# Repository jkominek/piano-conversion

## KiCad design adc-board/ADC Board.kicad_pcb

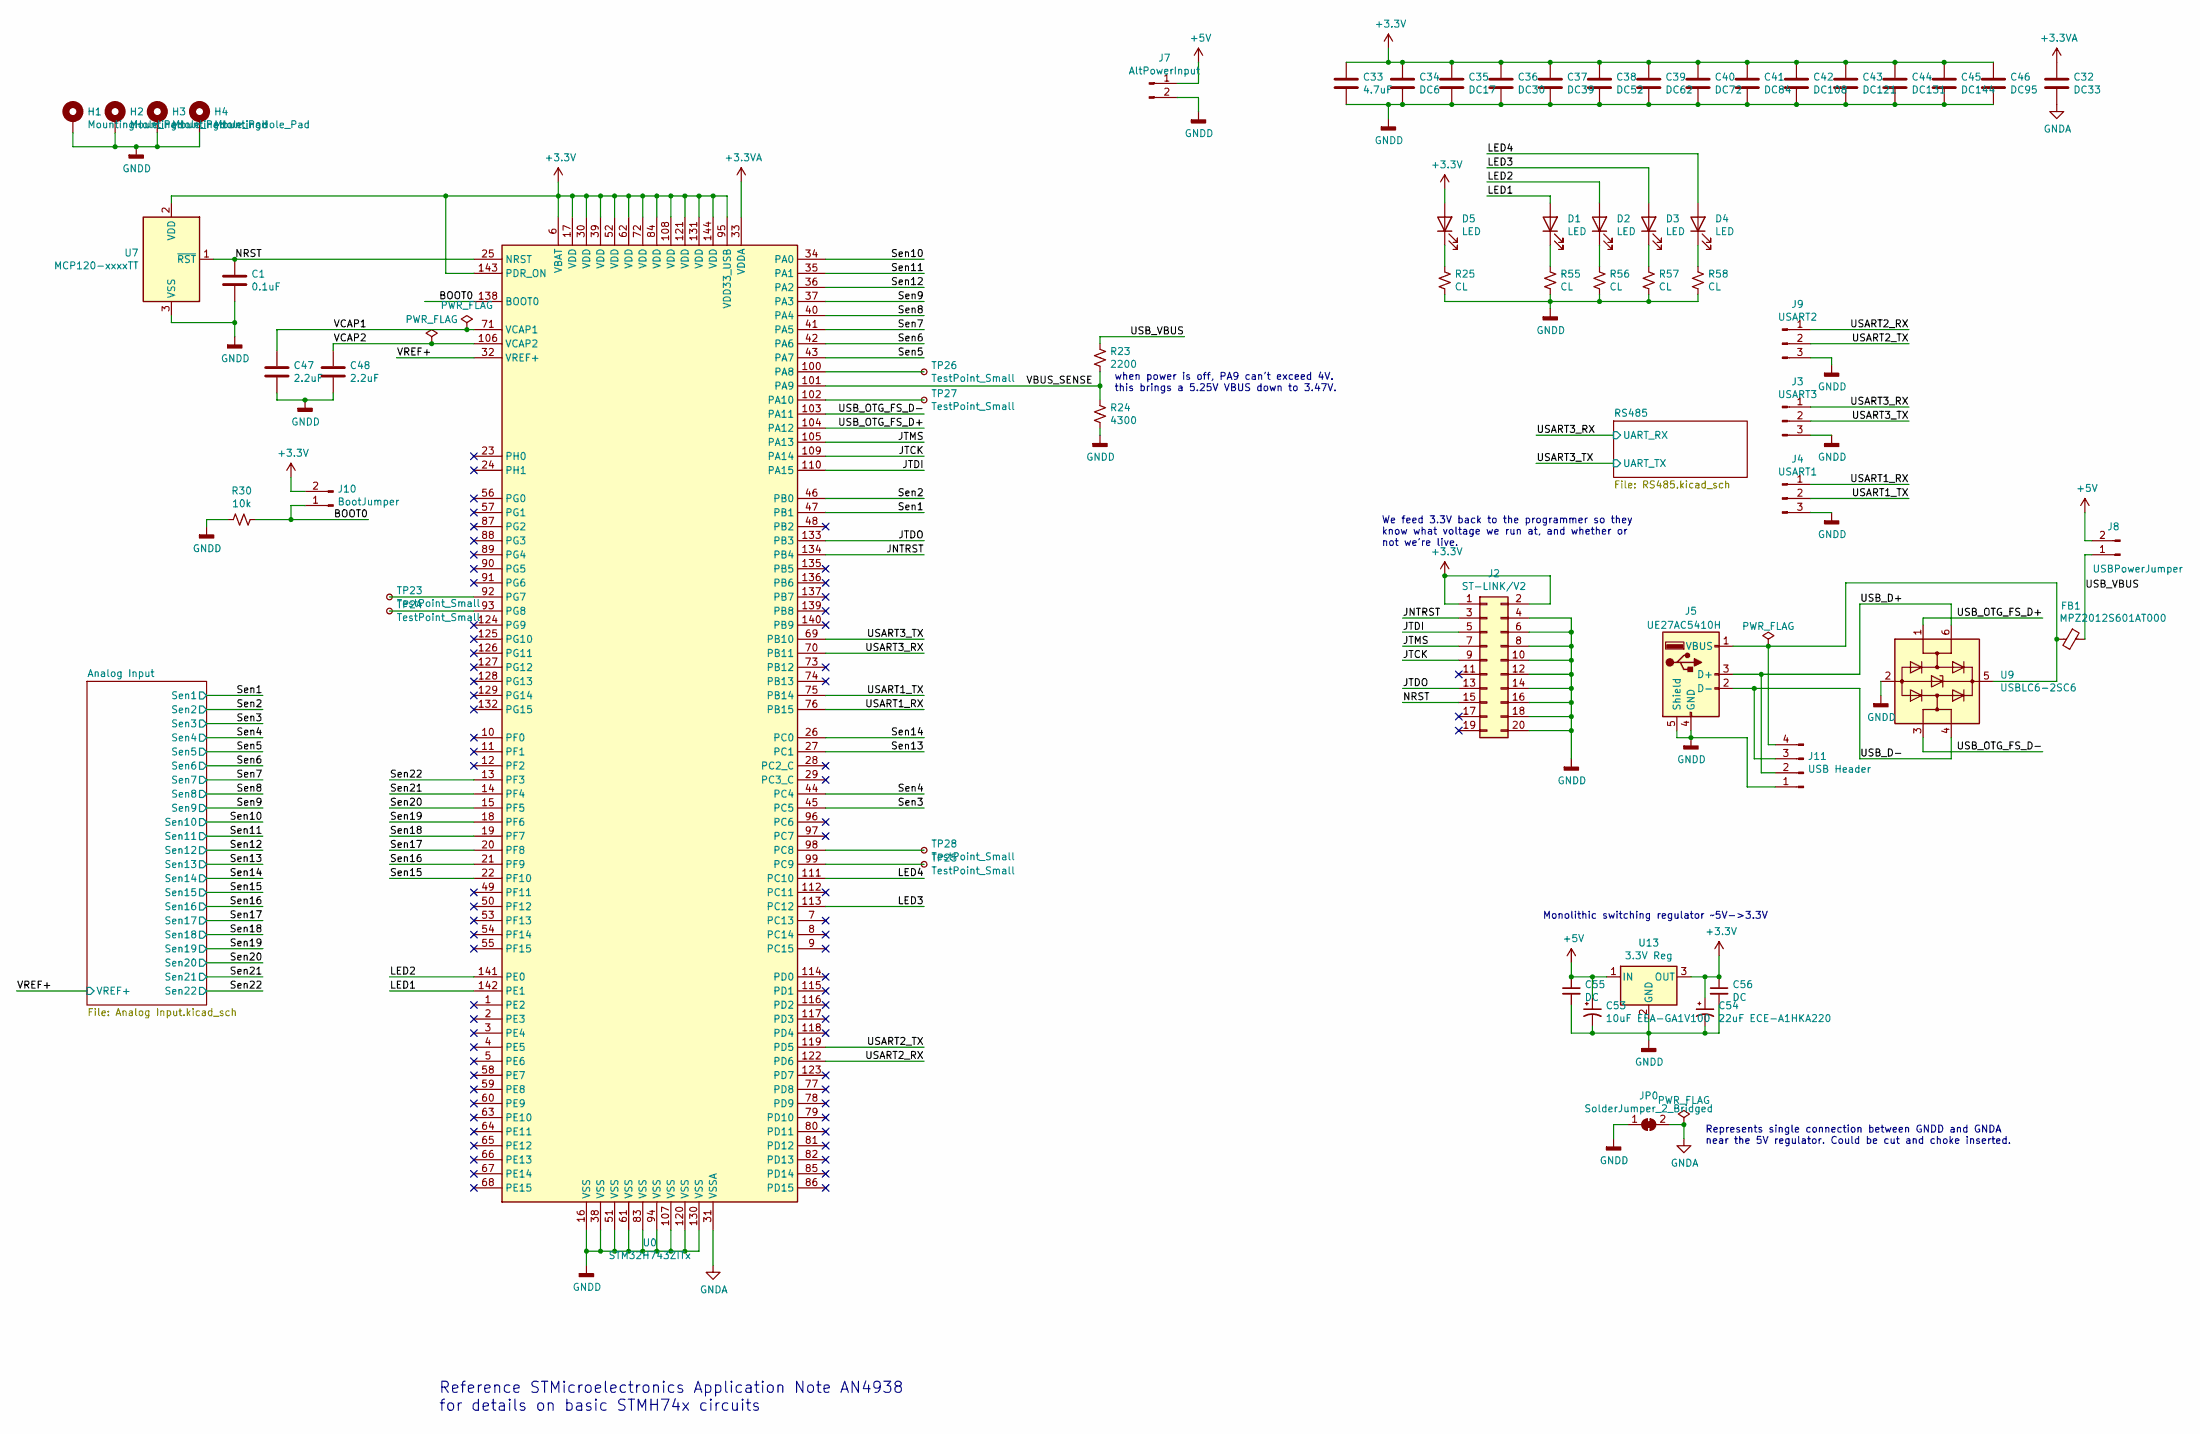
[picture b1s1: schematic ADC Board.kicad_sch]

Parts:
C1: 0.1uF; C_0805
C32: DC33; C_0805
C33: 4.7uF; C_0805
C34: DC6; C_0805
C35: DC17; C_0805
C36: DC30; C_0805
C37: DC39; C_0805
C38: DC52; C_0805
C39: DC62; C_0805
C40: DC72; C_0805
C41: DC84; C_0805
C42: DC108; C_0805
C43: DC121; C_0805
C44: DC131; C_0805
C45: DC144; C_0805
C46: DC95; C_0805
C47, C48: 2.2uF; C_0805
C53: 10uF EEA-GA1V100; CP_Elec_5x5.3
C54: 22uF ECE-A1HKA220; CP_Elec_6.3x5.3
C55, C56: DC; C_0805
D1, D2, D3, D4, D5: LED; LED_0805_HandSoldering
FB1: MPZ2012S601AT000; L_0805
H1, H2, H3, H4: MountingHole_Pad; MountingHole_3.2mm_M3_Pad_Via
J2: ST-LINK/V2; Pin_Header_Straight_2x10_Pitch2.54mm
J3: USART3; Pin_Header_Straight_1x03_Pitch2.54mm
J4: USART1; Pin_Header_Straight_1x03_Pitch2.54mm
J5: UE27AC5410H; USB_A_Molex_67643_Horizontal
J7: AltPowerInput; Pin_Header_Straight_1x02_Pitch2.54mm
J8: USBPowerJumper; Pin_Header_Straight_1x02_Pitch2.54mm
J9: USART2; Pin_Header_Straight_1x03_Pitch2.54mm
J10: BootJumper; Pin_Header_Straight_1x02_Pitch2.54mm
J11: USB Header; Pin_Header_Straight_1x04_Pitch2.54mm
JP0: SolderJumper_2_Bridged; SolderJumper-2_P1.3mm_Bridged_RoundedPad1.0x1.5mm
R23: 2200; R_0805
R24: 4300; R_0805
R25, R55, R56, R57, R58: CL; R_0805
R30: 10k; R_0805
TP23, TP24, TP25, TP26, TP27, TP28: TestPoint_Small; TestPoint_Pad_D1.5mm
U0: STM32H743ZITx; LQFP-144_20x20mm_Pitch0.5mm
U7: MCP120-xxxxTT; SOT-23
U9: USBLC6-2SC6; SOT-23-6_Handsoldering
U13: 3.3V Reg; TO-220-3_Vertical

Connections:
+3.3VA: C32.1, U0.33 (VDDA); also elsewhere on the board
+3V3: C33.1, C34.1, C35.1, C36.1, C37.1, C38.1, C39.1, C40.1, C41.1, C42.1, C43.1, C44.1, C45.1, C46.1, C54.1, C56.1, D5.2 (A), J2.1, J2.2, J10.2, U0.6 (VBAT), U0.17 (VDD), U0.30 (VDD), U0.39 (VDD), U0.52 (VDD), U0.62 (VDD), U0.72 (VDD), U0.84 (VDD), U0.95 (VDD33_USB), U0.108 (VDD), U0.121 (VDD), U0.131 (VDD), U0.143 (PDR_ON), U0.144 (VDD), U7.2 (VDD), U13.3 (OUT); also elsewhere on the board
+5V: C53.1, C55.1, J7.1, J8.2, U13.1 (IN); also elsewhere on the board
/BOOT0: J10.1, R30.1, U0.138 (BOOT0)
/JNTRST: J2.3, U0.134 (PB4)
/JTCK: J2.9, U0.109 (PA14)
/JTDI: J2.5, U0.110 (PA15)
/JTDO: J2.13, U0.133 (PB3)
/JTMS: J2.7, U0.105 (PA13)
/LED1: D1.2 (A), U0.142 (PE1)
/LED2: D2.2 (A), U0.141 (PE0)
/LED3: D3.2 (A), U0.113 (PC12)
/LED4: D4.2 (A), U0.111 (PC10)
/NRST: C1.1, J2.15, U0.25 (NRST), U7.1 (~RST)
/Sen1: U0.47 (PB1); also elsewhere on the board
/Sen2: U0.46 (PB0); also elsewhere on the board
/Sen3: U0.45 (PC5); also elsewhere on the board
/Sen4: U0.44 (PC4); also elsewhere on the board
/Sen5: U0.43 (PA7); also elsewhere on the board
/Sen6: U0.42 (PA6); also elsewhere on the board
/Sen7: U0.41 (PA5); also elsewhere on the board
/Sen8: U0.40 (PA4); also elsewhere on the board
/Sen9: U0.37 (PA3); also elsewhere on the board
/Sen10: U0.34 (PA0); also elsewhere on the board
/Sen11: U0.35 (PA1); also elsewhere on the board
/Sen12: U0.36 (PA2); also elsewhere on the board
/Sen13: U0.27 (PC1); also elsewhere on the board
/Sen14: U0.26 (PC0); also elsewhere on the board
/Sen15: U0.22 (PF10); also elsewhere on the board
/Sen16: U0.21 (PF9); also elsewhere on the board
/Sen17: U0.20 (PF8); also elsewhere on the board
/Sen18: U0.19 (PF7); also elsewhere on the board
/Sen19: U0.18 (PF6); also elsewhere on the board
/Sen20: U0.15 (PF5); also elsewhere on the board
/Sen21: U0.14 (PF4); also elsewhere on the board
/Sen22: U0.13 (PF3); also elsewhere on the board
/USART1_RX: J4.1, U0.76 (PB15)
/USART1_TX: J4.2, U0.75 (PB14)
/USART2_RX: J9.1, U0.122 (PD6)
/USART2_TX: J9.2, U0.119 (PD5)
/USART3_RX: J3.1, U0.70 (PB11); also elsewhere on the board
/USART3_TX: J3.2, U0.69 (PB10); also elsewhere on the board
/USB_D+: J5.3 (D+), J11.2, U9.6 (I/O1)
/USB_D-: J5.2 (D-), J11.3, U9.4 (I/O2)
/USB_OTG_FS_D+: U0.104 (PA12), U9.1 (I/O1)
/USB_OTG_FS_D-: U0.103 (PA11), U9.3 (I/O2)
/USB_VBUS: FB1.1, J8.1, R23.1
/VBUS_SENSE: R23.2, R24.1, U0.101 (PA9)
/VCAP1: C47.1, U0.71 (VCAP1)
/VCAP2: C48.1, U0.106 (VCAP2)
/VREF+: U0.32 (VREF+); also elsewhere on the board
GNDA: C32.2, JP0.2 (B), U0.31 (VSSA); also elsewhere on the board
GNDD: C1.2, C33.2, C34.2, C35.2, C36.2, C37.2, C38.2, C39.2, C40.2, C41.2, C42.2, C43.2, C44.2, C45.2, C46.2, C47.2, C48.2, C53.2, C54.2, C55.2, C56.2, H1.1, H2.1, H3.1, H4.1, J2.4, J2.6, J2.8, J2.10, J2.12, J2.14, J2.16, J2.18, J2.20, J3.3, J4.3, J5.4 (GND), J5.5 (Shield), J7.2, J9.3, J11.1, JP0.1 (A), R24.2, R25.2, R30.2, R55.2, R56.2, R57.2, R58.2, U0.16 (VSS), U0.38 (VSS), U0.51 (VSS), U0.61 (VSS), U0.83 (VSS), U0.94 (VSS), U0.107 (VSS), U0.120 (VSS), U0.130 (VSS), U7.3 (VSS), U9.2 (GND), U13.2 (GND); also elsewhere on the board
unnamed: D1.1 (K), R55.1
unnamed: D2.1 (K), R56.1
unnamed: D3.1 (K), R57.1
unnamed: D4.1 (K), R58.1
unnamed: D5.1 (K), R25.1
unnamed: FB1.2, J5.1 (VBUS), J11.4, U9.5 (VBUS)
unnamed: TP23.1, U0.92 (PG7)
unnamed: TP24.1, U0.93 (PG8)
unnamed: TP25.1, U0.99 (PC9)
unnamed: TP26.1, U0.100 (PA8)
unnamed: TP27.1, U0.102 (PA10)
unnamed: TP28.1, U0.98 (PC8)

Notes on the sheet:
Monolithic switching regulator ~5V->3.3V
We feed 3.3V back to the programmer so they know what voltage we run at, and whether or not we're live.
Reference STMicroelectronics Application Note AN4938 for details on basic STMH74x circuits
when power is off, PA9 can't exceed 4V. this brings a 5.25V VBUS down to 3.47V.
Represents single connection between GNDD and GNDA near the 5V regulator. Could be cut and choke inserted.

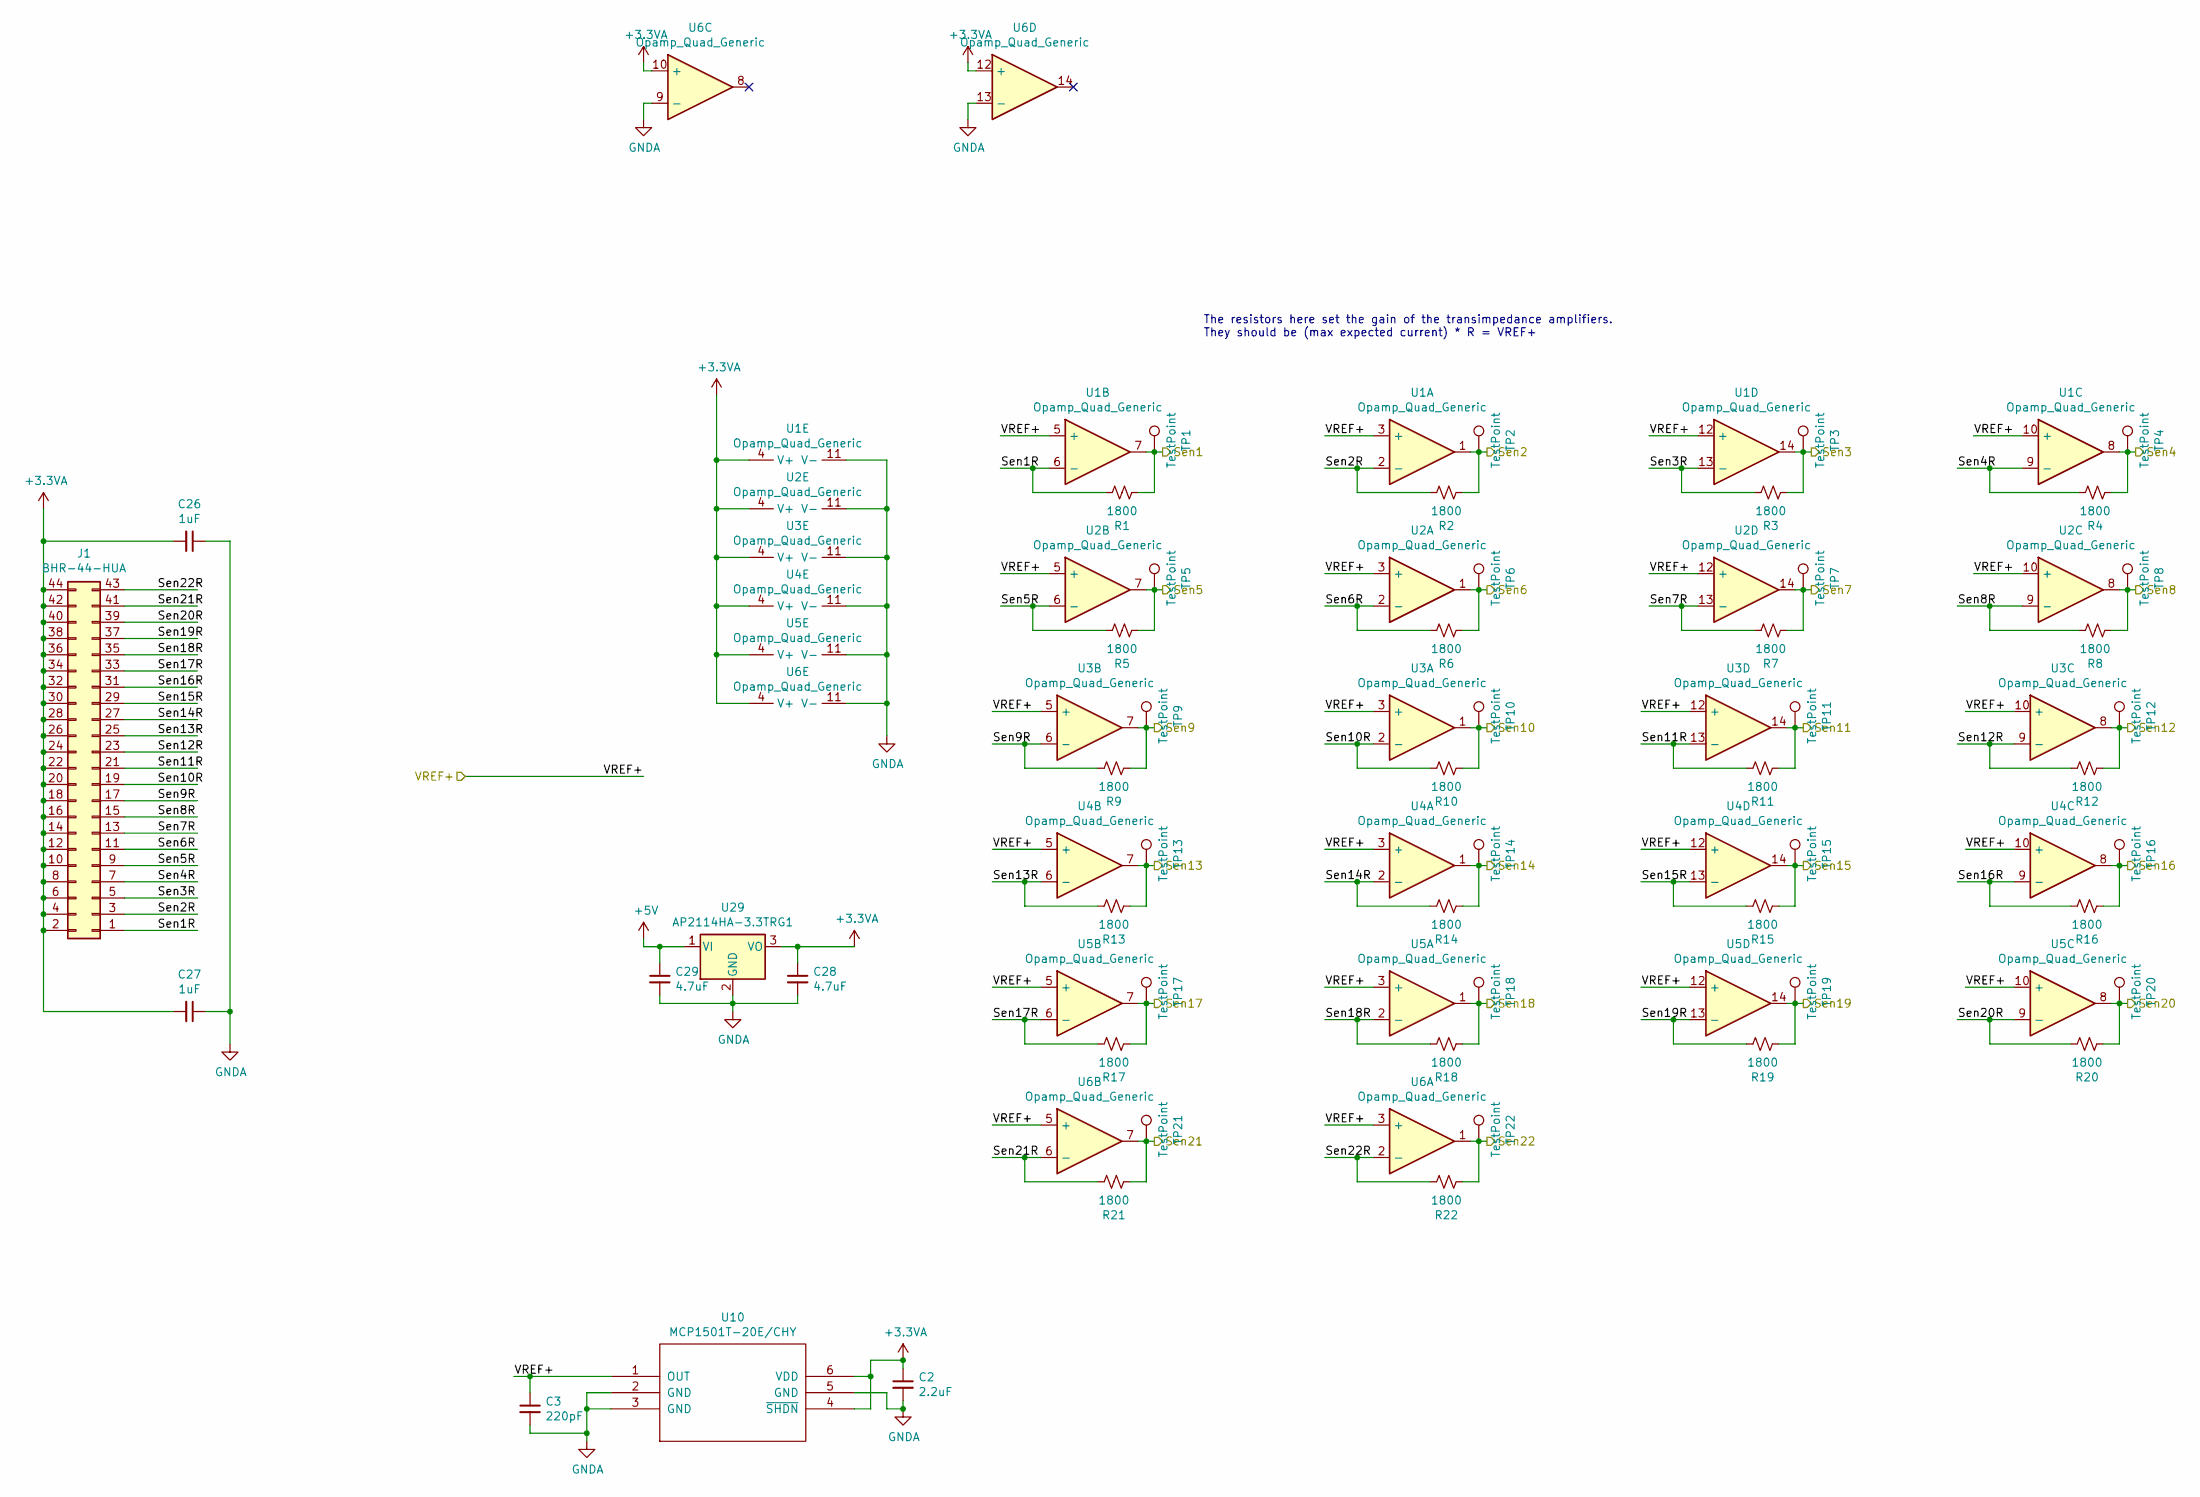
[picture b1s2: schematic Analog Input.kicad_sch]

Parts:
C2: 2.2uF; C_0805
C3: 220pF; C_0805
C26, C27: 1uF; C_0805
C28, C29: 4.7uF; C_0805
J1: BHR-44-HUA; Pin_Header_Angled_2x22_Pitch2.54mm
R1, R2, R3, R4, R5, R6, R7, R8, R9, R10, R11, R12, R13, R14, R15, R16, R17, R18, R19, R20, R21, R22: 1800; R_0805
TP1, TP2, TP3, TP4, TP5, TP6, TP7, TP8, TP9, TP10, TP11, TP12, TP13, TP14, TP15, TP16, TP17, TP18, TP19, TP20, TP21, TP22: TestPoint; TestPoint_Pad_D1.0mm
U1, U2, U3, U4, U5, U6: Opamp_Quad_Generic; TSSOP-14_4.4x5mm_Pitch0.65mm
U10: MCP1501T-20E/CHY; SOT-23-6_Handsoldering
U29: AP2114HA-3.3TRG1; SOT-223-3_TabPin2

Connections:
+3.3VA: C2.1, C26.2, C27.2, C28.1, J1.2, J1.4, J1.6, J1.8, J1.10, J1.12, J1.14, J1.16, J1.18, J1.20, J1.22, J1.24, J1.26, J1.28, J1.30, J1.32, J1.34, J1.36, J1.38, J1.40, J1.42, J1.44, U1.4 (V+), U2.4 (V+), U3.4 (V+), U4.4 (V+), U5.4 (V+), U6.4 (V+), U6.10 (+), U6.12 (+), U10.4 (~SHDN), U10.6 (VDD), U29.3 (VO); also elsewhere on the board
+5V: C29.1, U29.1 (VI); also elsewhere on the board
/Analog Input/Sen1R: J1.1, R1.1, U1.6 (-)
/Analog Input/Sen2R: J1.3, R2.1, U1.2 (-)
/Analog Input/Sen3R: J1.5, R3.1, U1.13 (-)
/Analog Input/Sen4R: J1.7, R4.1, U1.9 (-)
/Analog Input/Sen5R: J1.9, R5.1, U2.6 (-)
/Analog Input/Sen6R: J1.11, R6.1, U2.2 (-)
/Analog Input/Sen7R: J1.13, R7.1, U2.13 (-)
/Analog Input/Sen8R: J1.15, R8.1, U2.9 (-)
/Analog Input/Sen9R: J1.17, R9.1, U3.6 (-)
/Analog Input/Sen10R: J1.19, R10.1, U3.2 (-)
/Analog Input/Sen11R: J1.21, R11.1, U3.13 (-)
/Analog Input/Sen12R: J1.23, R12.1, U3.9 (-)
/Analog Input/Sen13R: J1.25, R13.1, U4.6 (-)
/Analog Input/Sen14R: J1.27, R14.1, U4.2 (-)
/Analog Input/Sen15R: J1.29, R15.1, U4.13 (-)
/Analog Input/Sen16R: J1.31, R16.1, U4.9 (-)
/Analog Input/Sen17R: J1.33, R17.1, U5.6 (-)
/Analog Input/Sen18R: J1.35, R18.1, U5.2 (-)
/Analog Input/Sen19R: J1.37, R19.1, U5.13 (-)
/Analog Input/Sen20R: J1.39, R20.1, U5.9 (-)
/Analog Input/Sen21R: J1.41, R21.1, U6.6 (-)
/Analog Input/Sen22R: J1.43, R22.1, U6.2 (-)
/Sen1: R1.2, TP1.1, U1.7; also elsewhere on the board
/Sen2: R2.2, TP2.1, U1.1; also elsewhere on the board
/Sen3: R3.2, TP3.1, U1.14; also elsewhere on the board
/Sen4: R4.2, TP4.1, U1.8; also elsewhere on the board
/Sen5: R5.2, TP5.1, U2.7; also elsewhere on the board
/Sen6: R6.2, TP6.1, U2.1; also elsewhere on the board
/Sen7: R7.2, TP7.1, U2.14; also elsewhere on the board
/Sen8: R8.2, TP8.1, U2.8; also elsewhere on the board
/Sen9: R9.2, TP9.1, U3.7; also elsewhere on the board
/Sen10: R10.2, TP10.1, U3.1; also elsewhere on the board
/Sen11: R11.2, TP11.1, U3.14; also elsewhere on the board
/Sen12: R12.2, TP12.1, U3.8; also elsewhere on the board
/Sen13: R13.2, TP13.1, U4.7; also elsewhere on the board
/Sen14: R14.2, TP14.1, U4.1; also elsewhere on the board
/Sen15: R15.2, TP15.1, U4.14; also elsewhere on the board
/Sen16: R16.2, TP16.1, U4.8; also elsewhere on the board
/Sen17: R17.2, TP17.1, U5.7; also elsewhere on the board
/Sen18: R18.2, TP18.1, U5.1; also elsewhere on the board
/Sen19: R19.2, TP19.1, U5.14; also elsewhere on the board
/Sen20: R20.2, TP20.1, U5.8; also elsewhere on the board
/Sen21: R21.2, TP21.1, U6.7; also elsewhere on the board
/Sen22: R22.2, TP22.1, U6.1; also elsewhere on the board
/VREF+: C3.1, U1.3 (+), U1.5 (+), U1.10 (+), U1.12 (+), U2.3 (+), U2.5 (+), U2.10 (+), U2.12 (+), U3.3 (+), U3.5 (+), U3.10 (+), U3.12 (+), U4.3 (+), U4.5 (+), U4.10 (+), U4.12 (+), U5.3 (+), U5.5 (+), U5.10 (+), U5.12 (+), U6.3 (+), U6.5 (+), U10.1 (OUT); also elsewhere on the board
GNDA: C2.2, C3.2, C26.1, C27.1, C28.2, C29.2, U1.11 (V-), U2.11 (V-), U3.11 (V-), U4.11 (V-), U5.11 (V-), U6.9 (-), U6.11 (V-), U6.13 (-), U10.2 (GND), U10.3 (GND), U10.5 (GND), U29.2 (GND); also elsewhere on the board

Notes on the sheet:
The resistors here set the gain of the transimpedance amplifiers. They should be (max expected current) * R =~{} VREF+

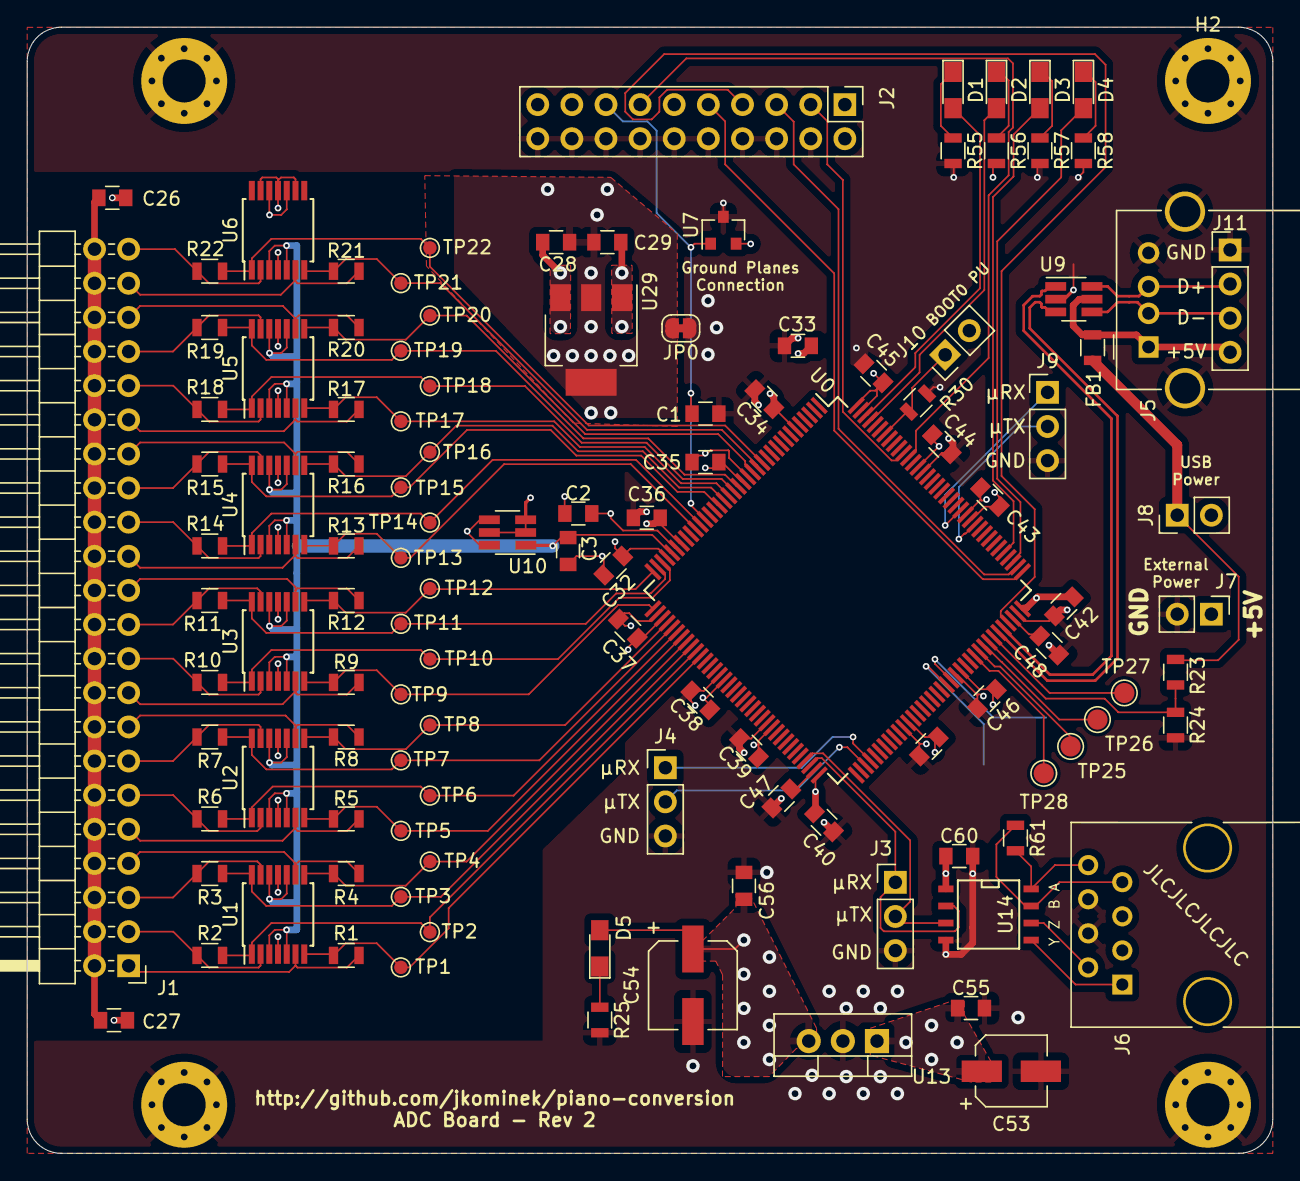
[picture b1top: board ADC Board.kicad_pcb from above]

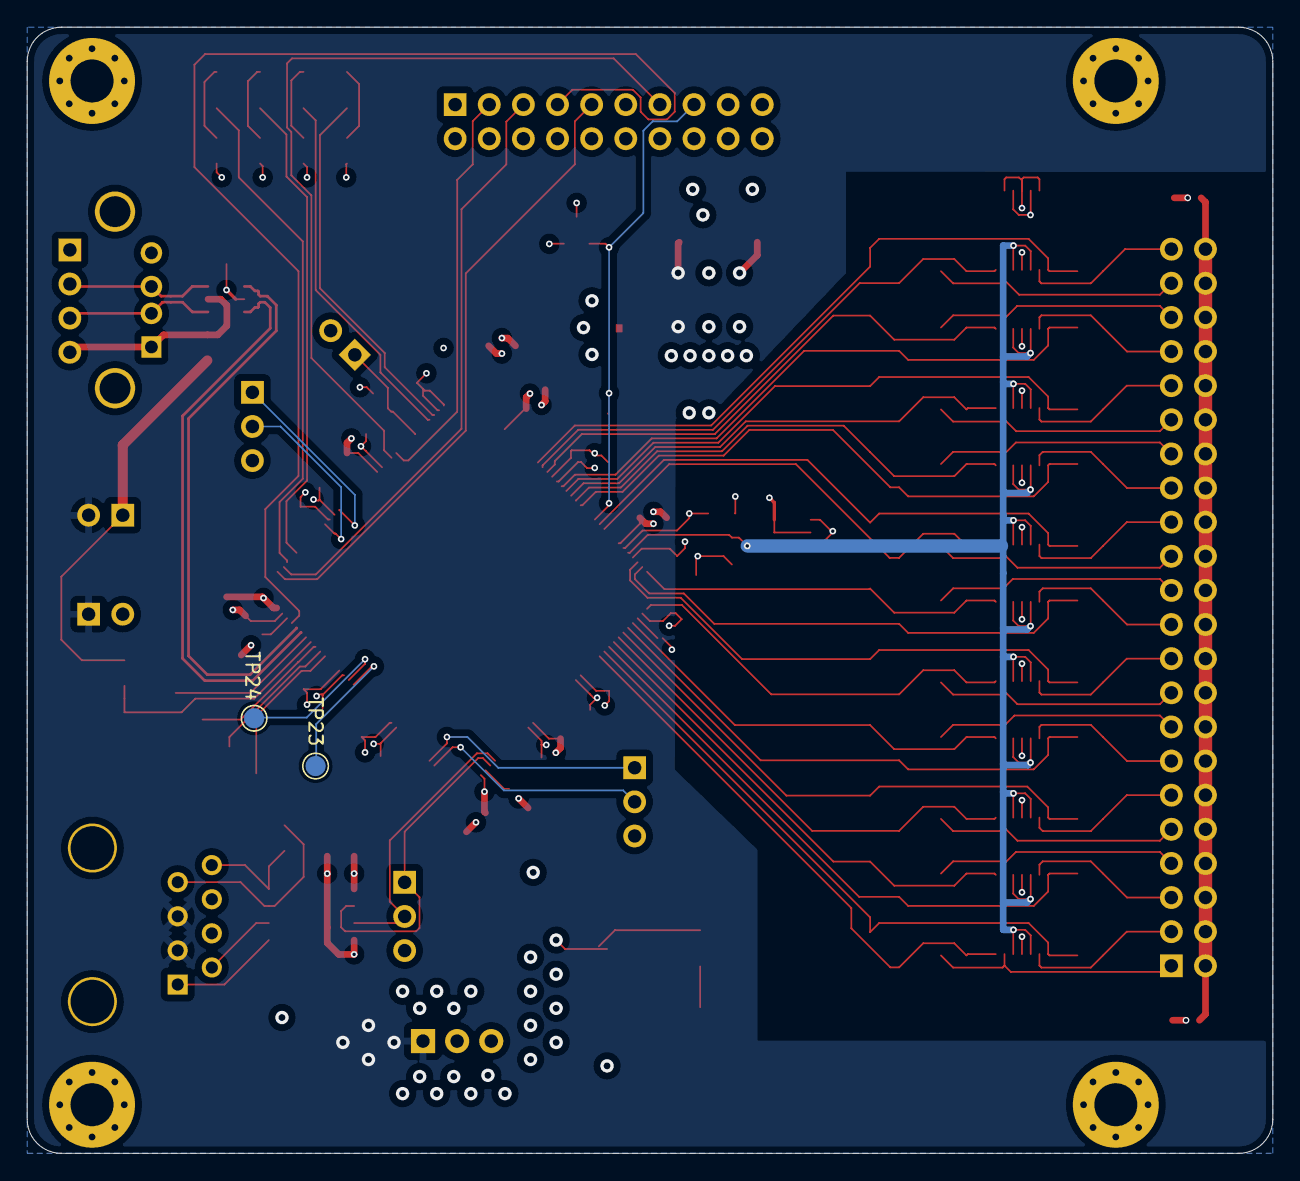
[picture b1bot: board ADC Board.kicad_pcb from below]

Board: 4 copper layers, 92.7 x 83.8 mm, 123 parts (2 on the bottom side), 91 nets.

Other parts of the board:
C60: DC; C_0805
J6: 54601-908WPLF; RJ45_8
R61: 120; R_0805
U14: ISL83490; SOIC-8-N

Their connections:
+3V3: C60.1, U14.1 (VCC); also elsewhere on the board
+5V: J6.3, J6.5; also elsewhere on the board
/RS485/A: J6.8, R61.2, U14.8 (A)
/RS485/B: J6.7, R61.1, U14.7 (B)
/RS485/Y: J6.1, U14.5 (Y)
/RS485/Z: J6.2, U14.6 (Z)
/USART3_RX: U14.2 (RO); also elsewhere on the board
/USART3_TX: U14.3 (DI); also elsewhere on the board
GNDD: C60.2, J6.4, J6.6, U14.4 (GND); also elsewhere on the board

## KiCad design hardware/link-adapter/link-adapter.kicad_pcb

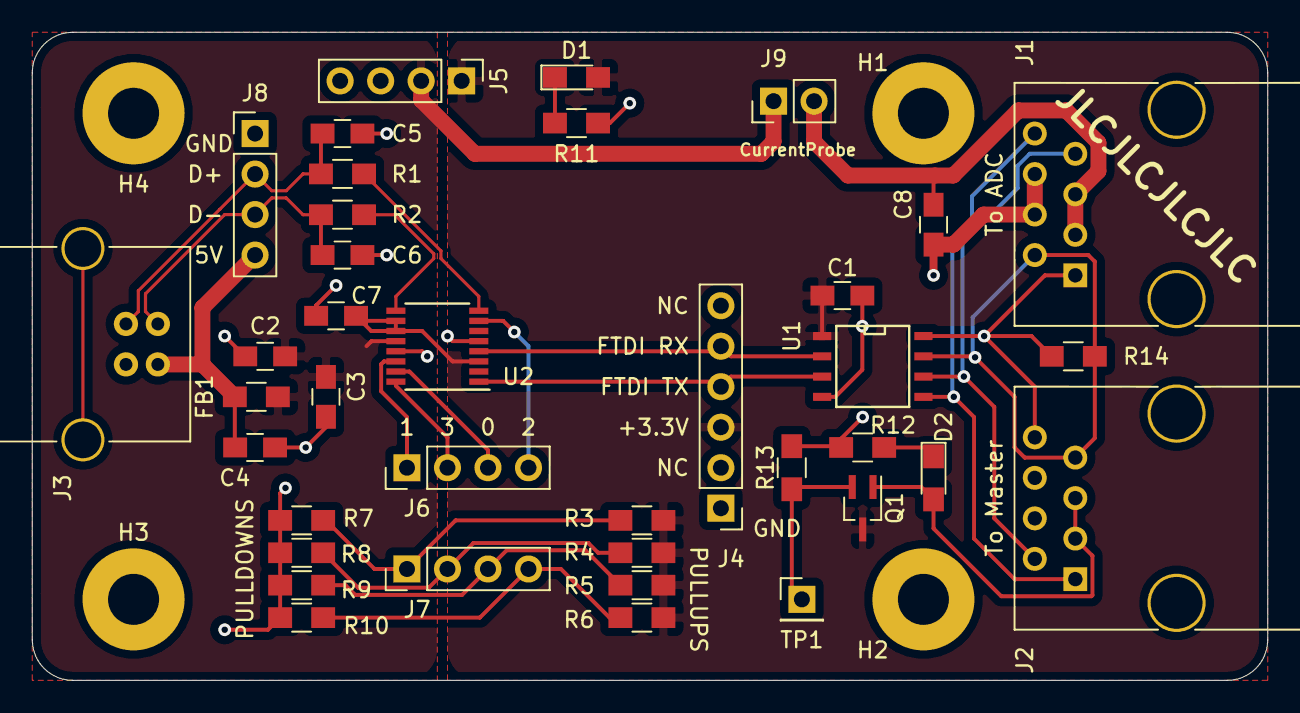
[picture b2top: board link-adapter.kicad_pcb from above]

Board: 2 copper layers, 77.5 x 40.6 mm, 42 parts (0 on the bottom side), 27 nets.

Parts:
C1, C2, C7, C8: 0.1uF; C_0805_HandSoldering
C3: 4.7uF; C_0805_HandSoldering
C4: 10nF; C_0805_HandSoldering
C5, C6: 47pF; C_0805_HandSoldering
D1, D2: LED; LED_0805_HandSoldering
FB1: MPZ2012S601AT000‎; L_0805_HandSoldering
H1, H2, H3, H4: MountingHole_Pad; MountingHole_3.2mm_M3_Pad
J1: ToADC; RJ45_8
J2: ToMaster; RJ45_8
J3: USB_B
J4: FTDI Header; Pin_Header_Straight_1x06_Pitch2.54mm
J5: PowerJumper; Pin_Header_Straight_1x04_Pitch2.54mm
J6: CBUS; Pin_Header_Straight_1x04_Pitch2.54mm
J7: FORLED; Pin_Header_Straight_1x04_Pitch2.54mm
J8: AltUSB; Pin_Header_Straight_1x04_Pitch2.54mm
J9: CurrentProbe; Pin_Header_Straight_1x02_Pitch2.54mm
Q1: NX7002BKW; SOT-323_SC-70_Handsoldering
R1, R2: 27; R_0805_HandSoldering
R3, R4, R5, R6, R7, R8, R9, R10, R13: 6000; R_0805_HandSoldering
R11: 620; R_0805_HandSoldering
R12: 3000; R_0805_HandSoldering
R14: 120; R_0805_HandSoldering
TP1: MPWRGOOD; Pin_Header_Straight_1x01_Pitch2.54mm
U1: ISL83490; SOIC-8-N
U2: FT230XS; SSOP-16_3.9x4.9mm_Pitch0.635mm

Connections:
+3V3: C1.1, C7.1, D1.2, J4.3, J5.1, Q1.3, R3.1, R4.1, R5.1, R6.1, U1.1, U2.3, U2.10, U2.11
+5V: C2.1, C3.1, FB1.1, J5.2, J9.1, U2.12
/A: J1.1, J2.8, R14.2, U1.8
/B: J1.2, J2.7, R14.1, U1.7
/CBUS0: J6.3, U2.15
/CBUS1: J6.1, U2.14
/CBUS2: J6.4, U2.7
/CBUS3: J6.2, U2.16
/D+: C5.1, J3.3, J8.2, R1.2
/D-: C6.1, J3.2, J8.3, R2.2
/J6_1: J7.1, R3.2, R7.1
/J6_2: J7.2, R4.2, R8.1
/J6_3: J7.3, R5.2, R9.1
/J6_4: J7.4, R6.2, R10.1
/RX: J4.5, U1.2, U2.4
/TX: J4.4, U1.3, U2.1
/USB5V: C4.1, FB1.2, J3.1, J8.4
/USBD+: R1.1, U2.8
/USBD-: R2.1, U2.9
/Y: J1.8, J2.1, U1.5
/Z: J1.7, J2.2, U1.6
GND: C1.2, C2.2, C3.2, C4.2, C5.2, C6.2, C7.2, C8.2, H1.1, H2.1, H3.1, H4.1, J1.4, J1.6, J2.4, J2.6, J3.4, J4.1, J5.4, J8.1, R7.2, R8.2, R9.2, R10.2, R11.2, R12.2, R13.2, U1.4, U2.5, U2.13
unnamed: C8.1, J1.3, J1.5, J9.2
unnamed: D1.1, R11.1
unnamed: D2.1, R12.1
unnamed: D2.2, J2.3, J2.5, Q1.1
unnamed: Q1.2, R13.1, TP1.1

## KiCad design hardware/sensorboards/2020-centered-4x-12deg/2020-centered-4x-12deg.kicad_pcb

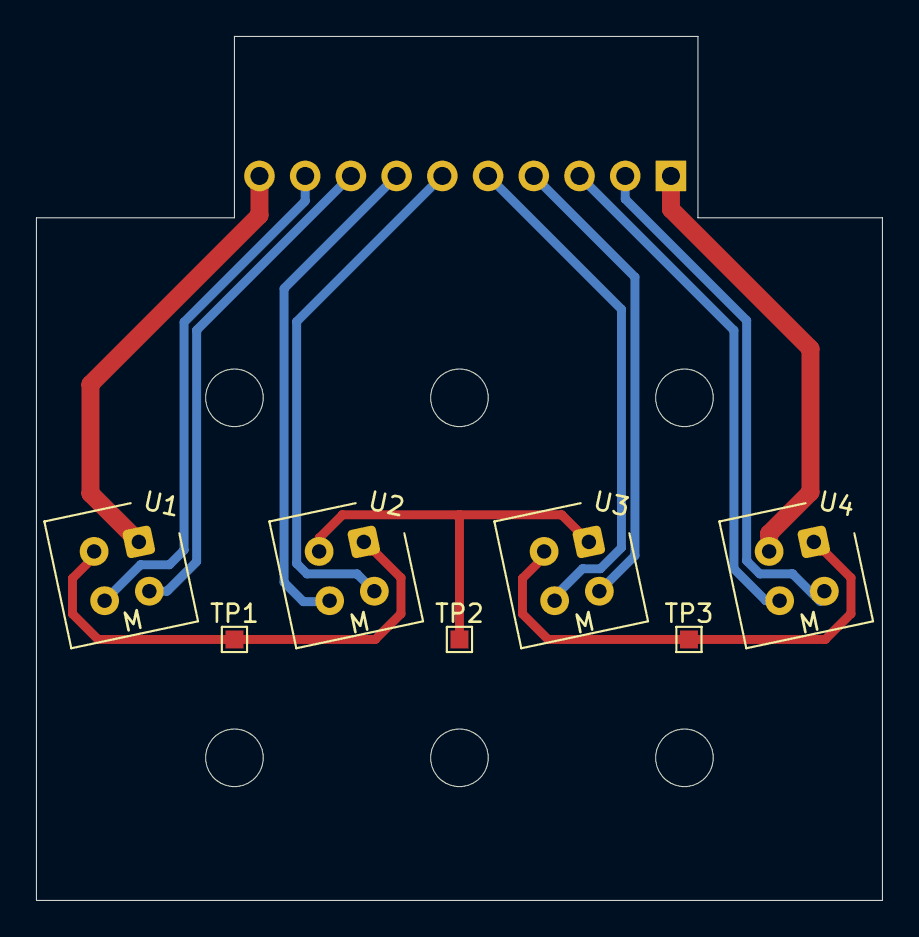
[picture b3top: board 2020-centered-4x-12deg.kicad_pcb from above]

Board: 2 copper layers, 47.0 x 48.0 mm, 14 parts (1 on the bottom side), 13 nets.

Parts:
H1, H2, H3, H4, H5, H6: MountingHole; MountingHole_3.2mm_M3
J1: Conn_01x10_Male; Pin_Header_Angled_1x10_Pitch2.54mm
TP1, TP2, TP3: TestPoint; TestPoint_Pad_1.0x1.0mm
U1, U2, U3, U4: CNY70; Vishay_CNY70_12DegRotation

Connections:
/C1: J1.9, U1.3
/C2: J1.7, U2.3
/C3: J1.5, U3.3
/C4: J1.3, U4.3
/E1: J1.8, U1.4
/E2: J1.6, U2.4
/E3: J1.4, U3.4
/E4: J1.2, U4.4
/NEG: J1.1, U4.2
/POS: J1.10, U1.1
unnamed: TP1.1, U1.2, U2.1
unnamed: TP2.1, U2.2, U3.1
unnamed: TP3.1, U3.2, U4.1

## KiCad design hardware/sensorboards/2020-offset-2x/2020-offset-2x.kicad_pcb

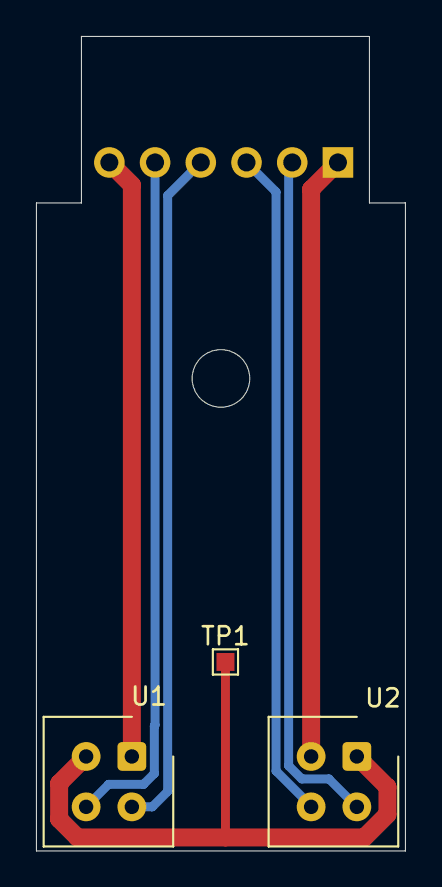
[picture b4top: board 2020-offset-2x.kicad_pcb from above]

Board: 2 copper layers, 20.5 x 45.2 mm, 5 parts (1 on the bottom side), 7 nets.

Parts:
H1: MountingHole; MountingHole_3.2mm_M3
J1: Conn_01x06_Male; Pin_Header_Angled_1x06_Pitch2.54mm
TP1: TestPoint; TestPoint_Pad_1.0x1.0mm
U1, U2: CNY70; Vishay_CNY70

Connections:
/C1: J1.5, U1.3 (C)
/C2: J1.3, U2.3 (C)
/E1: J1.4, U1.4 (E)
/E2: J1.2, U2.4 (E)
/NEG: J1.1, U2.2 (K)
/POS: J1.6, U1.1 (A)
unnamed: TP1.1, U1.2 (K), U2.1 (A)

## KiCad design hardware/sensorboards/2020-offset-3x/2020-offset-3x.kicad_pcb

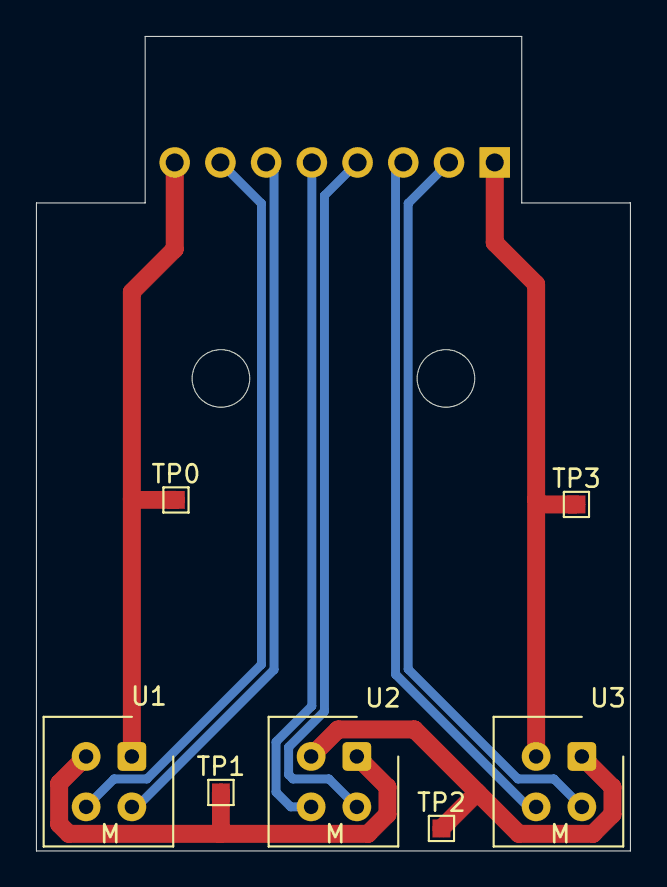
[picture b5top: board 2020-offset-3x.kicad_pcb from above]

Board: 2 copper layers, 33.0 x 45.2 mm, 10 parts (1 on the bottom side), 10 nets.

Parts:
H1, H2: MountingHole; MountingHole_3.2mm_M3
J1: Conn_01x10_Male; PinHeader_1x08_P2.54mm_Horizontal
TP0, TP1, TP2, TP3: TestPoint; TestPoint_Pad_1.0x1.0mm
U1, U2, U3: CNY70; Vishay_CNY70

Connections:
/C1: J1.7, U1.3 (C)
/C2: J1.5, U2.3 (C)
/C3: J1.3, U3.3 (C)
/E1: J1.6, U1.4 (E)
/E2: J1.4, U2.4 (E)
/E3: J1.2, U3.4 (E)
/NEG: J1.1, TP3.1, U3.2 (K)
/POS: J1.8, TP0.1, U1.1 (A)
unnamed: TP1.1, U1.2 (K), U2.1 (A)
unnamed: TP2.1, U2.2 (K), U3.1 (A)
